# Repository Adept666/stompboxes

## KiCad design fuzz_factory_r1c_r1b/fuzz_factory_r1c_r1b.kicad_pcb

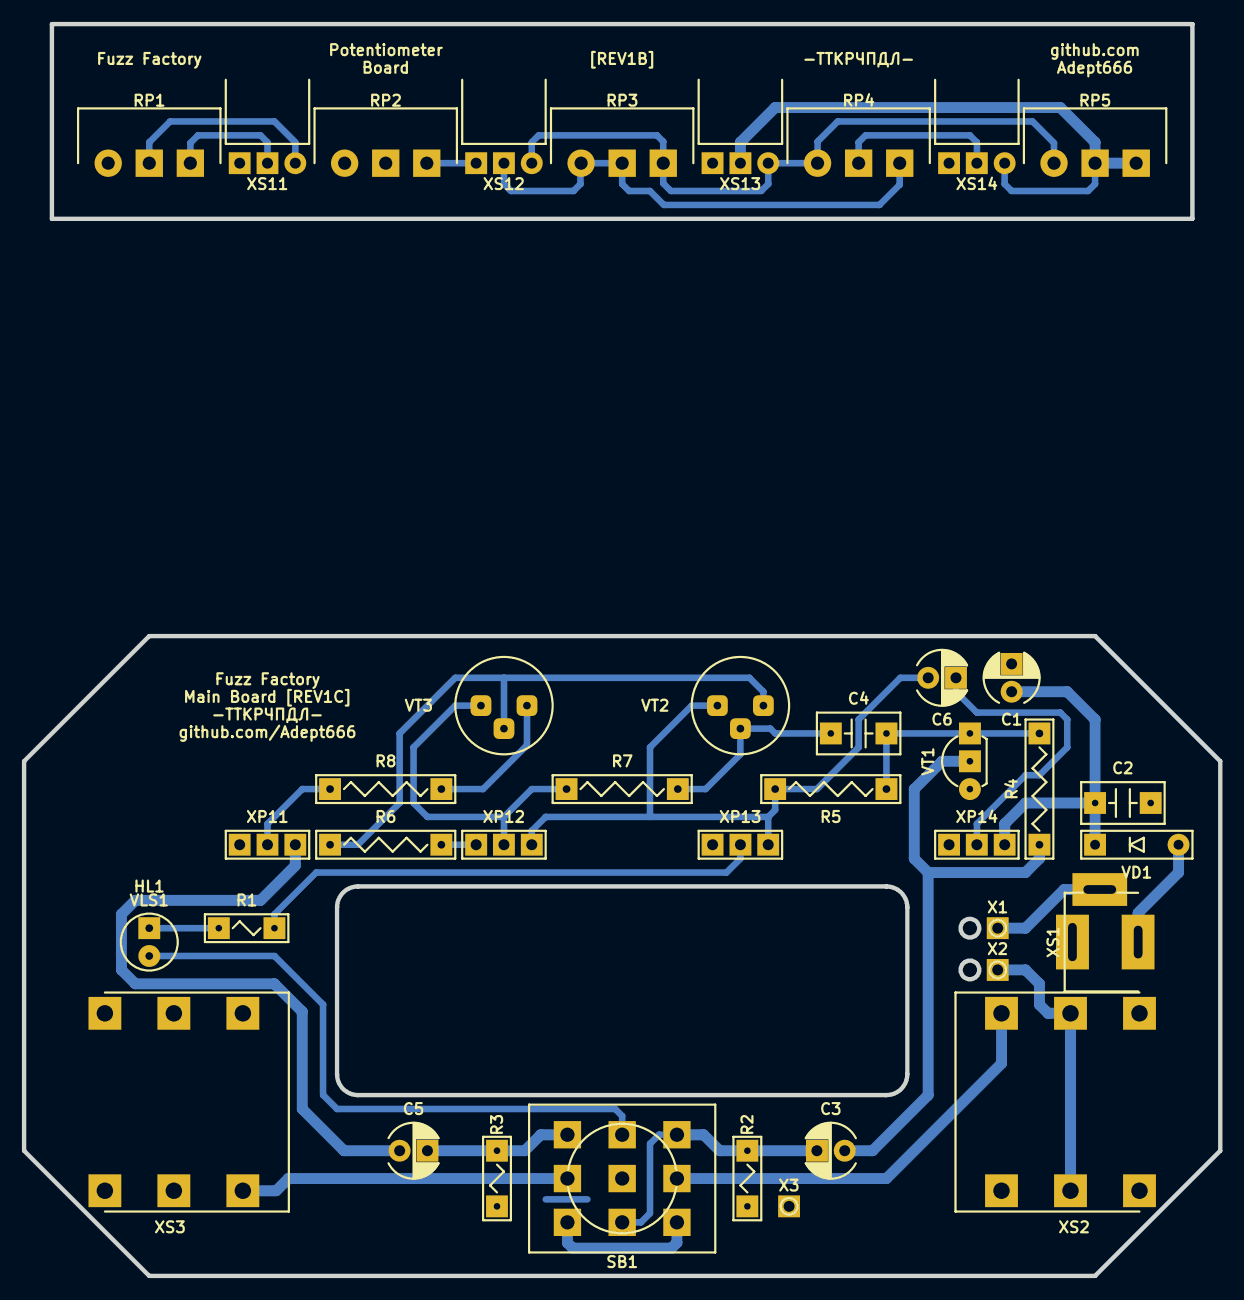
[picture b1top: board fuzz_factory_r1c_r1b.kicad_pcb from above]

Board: 2 copper layers, 109.2 x 114.3 mm, 42 parts (0 on the bottom side), 31 nets.

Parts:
C1: 107; CP-RADIAL-D05.0-P02.0-CLS
C2, C4: 104; C-DISK-D04.2-T03.0-P05.08-d0.5
C3, C5, C6: 106; CP-RADIAL-D05.0-P02.0-CLS
GB1: PP3; B-PP3-HV
HL1: FYL-5013UWC; LED-ROUND-05.0-UNI-SH-SPACER-PNL-5.3
R1: 103; R-MFR-12
R2: 105; R-MFR-12
R3: 224; R-MFR-12
R4: 224; R-MFR-25
R5: 103; R-MFR-25
R6: 471; R-MFR-25
R7: 473; R-MFR-25
R8: 512; R-MFR-25
RP1, RP5: B5K; RP-RK1233N1-L15-KC
RP2, RP3, RP4: B10K; RP-RK1233N1-L15-KC
SB1: PBS-24-302SP; SW-PBS-24-302SP-2.5
VD1: 5817; P-DO-41
VE1: B013; B013_C1
VLS1: BR-17.8; VLS-BR
VT1: 3904; P-TO-92-E-B-C
VT2, VT3: МП40; P-КТЮ-3-6
X1: +; CON-PAD-S-1.0-2.0
X2: -; CON-PAD-S-1.0-2.0
X3: COM; CON-PAD-S-1.0-2.0
XP11, XP12, XP13, XP14: PLS-03; CON-PLS-03
XS1: DC-005; CON-DC-005
XS2, XS3: PJ-644C; CON-PJ-644C
XS11, XS12, XS13, XS14: PBS-03R; CON-PBS-03R

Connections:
/IN-CIR: C3.-, R2.2, SB1.NC2, SB1.NO3
/IN-CON: SB1.COM3, XS2.T
/LED: HL1.C, SB1.NO2
/MB1: R8.1, XP11.2
/MB2: C5.+, XP11.1
/MB3: R6.1, XP12.3
/MB4: R7.2, VT3.E, XP12.2
/MB5: C6.+, R5.2, VT2.E, XP12.1, XP13.1
/MB7: C6.-, XP14.2
/OUT-CIR: C5.-, R3.2, SB1.NO1
/OUT-CON: SB1.COM1, XS3.T
/PB1: RP1.3, XS11.2
/PB2: RP1.2, XS11.1
/PB3: RP2.3, XS12.3
/PB4: RP3.1, RP3.2, RP4.3, XS12.2
/PB5: RP3.3, RP4.1, RP5.1, XS12.1, XS13.1
/PB7: RP4.2, XS14.2
/PBCOM: RP1.1, RP2.1, RP2.2, XS11.3, XS13.3, XS14.3
/PBV: RP5.2, RP5.3, XS13.2, XS14.1
/PP3-NEG: X2.1, XS2.R, XS2.RN
/PP3-POS: X1.1, XS1.SN
COM: C1.-, C2.2, R2.1, R3.1, SB1.COM2, VT1.E, X3.1, XP11.3, XP14.3, XS1.C, XS2.S, XS2.SN, XS2.TN, XS3.R, XS3.RN, XS3.S, XS3.SN
unnamed: C3.+, R4.1, VT1.B
unnamed: C4.1, R4.2, R5.1, VT1.C
unnamed: C4.2, R7.1, VT2.B
unnamed: HL1.A, R1.1
unnamed: R6.2, VT2.C, VT3.B
unnamed: R8.2, VT3.C
unnamed: SB1.NC1, SB1.NC3
unnamed: VD1.A, XS1.S
V: C1.+, C2.1, R1.2, VD1.C, XP13.2, XP14.1

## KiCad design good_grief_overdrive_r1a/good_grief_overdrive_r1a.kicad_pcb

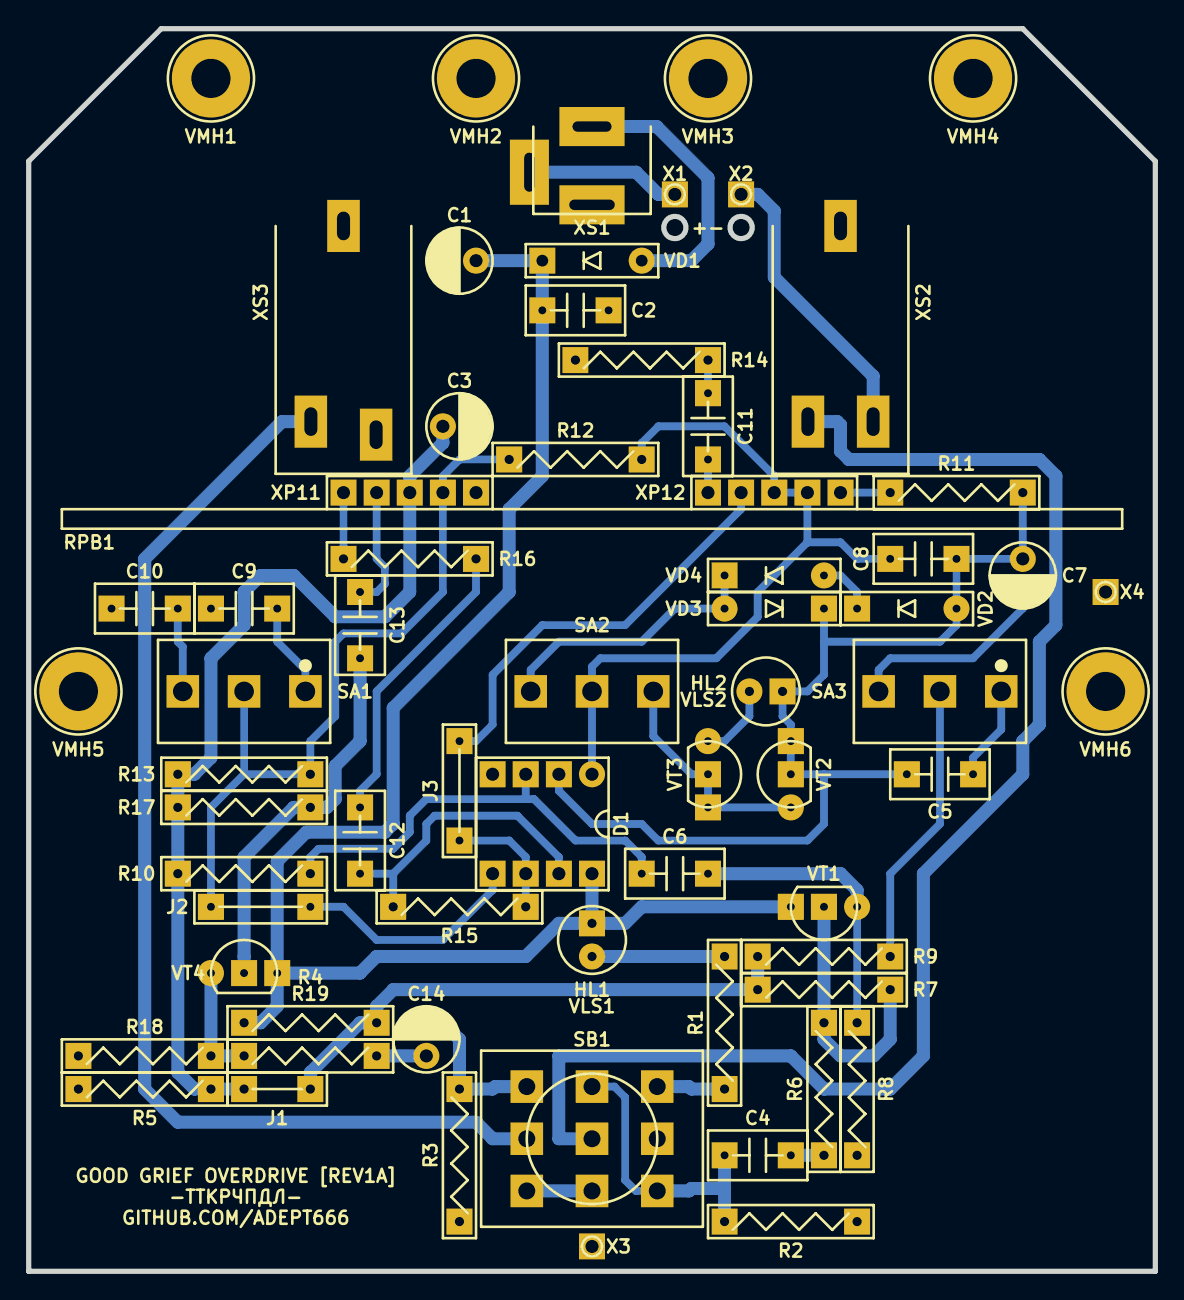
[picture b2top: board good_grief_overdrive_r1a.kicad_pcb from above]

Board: 2 copper layers, 86.4 x 95.3 mm, 69 parts (0 on the bottom side), 40 nets.

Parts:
C1, C3: 476; CP-RADIAL-D05.0-P02.0-CLS
C2, C4, C13: 104; C-DISK-D04.2-T03.0-P05.08-d0.5
C5: 224; C-DISK-D04.2-T03.0-P05.08-d0.5
C6, C12: 105; C-DISK-D04.2-T03.0-P05.08-d0.5
C7, C14: 106; CP-RADIAL-D05.0-P02.0-CLS
C8: 470; C-DISK-D04.2-T03.0-P05.08-d0.5
C9: 154; C-DISK-D04.2-T03.0-P05.08-d0.5
C10: 683; C-DISK-D04.2-T03.0-P05.08-d0.5
C11: 334; C-DISK-D04.2-T03.0-P05.08-d0.5
D1: 833; P-DIP-08
GB1: PP3; B-PP3-HV
HL1: FYL-5013UWC; LED-ROUND-05.0-UNI-SH-SPACER-PNL-5.3
HL2: FYL-5013URC; LED-ROUND-05.0-UNI-SH-SPACER-PNL-5.3
J1: 0.6; J-TH-d0.6-P05.08
J2, J3: 0.5; J-TH-d0.5-P07.62
R1, R3, R4, R5, R8, R13, R18: 103; R-MFR-25
R2: 105; R-MFR-25
R6, R9, R12, R15, R16: 102; R-MFR-25
R7, R17: 564; R-MFR-25
R10, R11: 223; R-MFR-25
R14: 331; R-MFR-25
R19: 101; R-MFR-25
RPB1: B100K-B5K-A500K; RPB-1590BB-18-3x17-1.5-PNL-7.4-2.6
SA1, SA3: MTS-102-A2; SW-MTS-102-A2-2.5-PNL-6.4
SA2: MTS-103-A2; SW-MTS-103-A2-2.5-PNL-6.4
SB1: PBS-24-302SP; SW-PBS-24-302SP-2.5-PNL-13.0
VD1: 5817; P-DO-41
VD2, VD3, VD4: 4148; P-DO-35
VE1: 1590BB; 1590BB_A1
VLS1, VLS2: BR-12.7; VLS-BR
VMH1, VMH2, VMH3, VMH4, VMH5, VMH6: DI5M3x18; VMH-STA-DA5-PNL-3.0
VT1, VT4: MPSA18; P-TO-92-E-B-C
VT2, VT3: 7000; P-TO-92-S-G-D
X1: +; CON-PAD-S-1.0-2.0
X2: -; CON-PAD-S-1.0-2.0
X3, X4: COM; CON-PAD-S-1.0-2.0
XS1: DC-005; CON-DC-005
XS2: ST-008S-04; CON-ST-008X-04
XS3: ST-008S-05; CON-ST-008X-05

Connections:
/IN-CIR: C4.1, R2.2, SB1.NC3, SB1.NO2
/IN-CON: SB1.COM2, XS2.T
/LED: R1.1, SB1.NO3
/OUT-CIR: C14.-, R3.2, SB1.NO1
/OUT-CON: SB1.COM1, XS3.T
/PP3-NEG: X2.1, XS2.R
/PP3-POS: X1.1, XS1.SN
/RP21: D1.5, J2.J, R12.2, R13.1, RPB1.21, SA1.COM
/RP23: D1.6, J3.J, R15.1, RPB1.23
COM: C1.-, C2.2, C3.-, C9.2, C10.2, D1.4, R2.1, R3.1, R5.1, R8.1, R14.1, R18.1, SB1.COM3, VMH1.0, VMH2.0, VMH3.0, VMH4.0, VMH5.0, VMH6.0, X3.1, X4.1, XS1.C, XS2.S, XS3.S
unnamed: C4.2, R6.1
unnamed: C5.1, C7.+, C8.1, D1.2, HL2.A, R11.1, VD2.A, VD3.C, VT2.D, VT2.G
unnamed: C5.2, SA3.NC
unnamed: C6.1, R8.2, VT1.E
unnamed: C6.2, D1.3, R10.2
unnamed: C7.-, SA3.NO
unnamed: C8.2, D1.1, R12.1, RPB1.32, RPB1.33, SA2.COM
unnamed: C9.1, SA1.NC
unnamed: C10.1, SA1.NO
unnamed: C11.1, RPB1.22
unnamed: C11.2, R14.2
unnamed: C12.1, D1.7, R15.2
unnamed: C12.2, R16.1
unnamed: C13.1, RPB1.12
unnamed: C13.2, R17.2, VT4.B
unnamed: C14.+, R19.2
unnamed: HL1.C, R1.2
unnamed: HL2.C, VT3.S
unnamed: R6.2, R7.2, VT1.B
unnamed: R9.2, SA3.COM
unnamed: R11.2, RPB1.31
unnamed: R16.2, RPB1.13
unnamed: R18.2, R19.1, VT4.E
unnamed: SA2.NO_1, VT2.S, VT3.D, VT3.G
unnamed: SA2.NO_2, VD3.A, VD4.C
unnamed: SB1.NC1, SB1.NC2
unnamed: VD1.A, XS1.S
unnamed: VD2.C, VD4.A
V: C1.+, C2.1, D1.8, HL1.A, R4.2, VD1.C, VT1.C, VT4.C
VREF: C3.+, J1.J, R4.1, R5.2, R7.1, R9.1, R10.1, R13.2, R17.1, RPB1.11

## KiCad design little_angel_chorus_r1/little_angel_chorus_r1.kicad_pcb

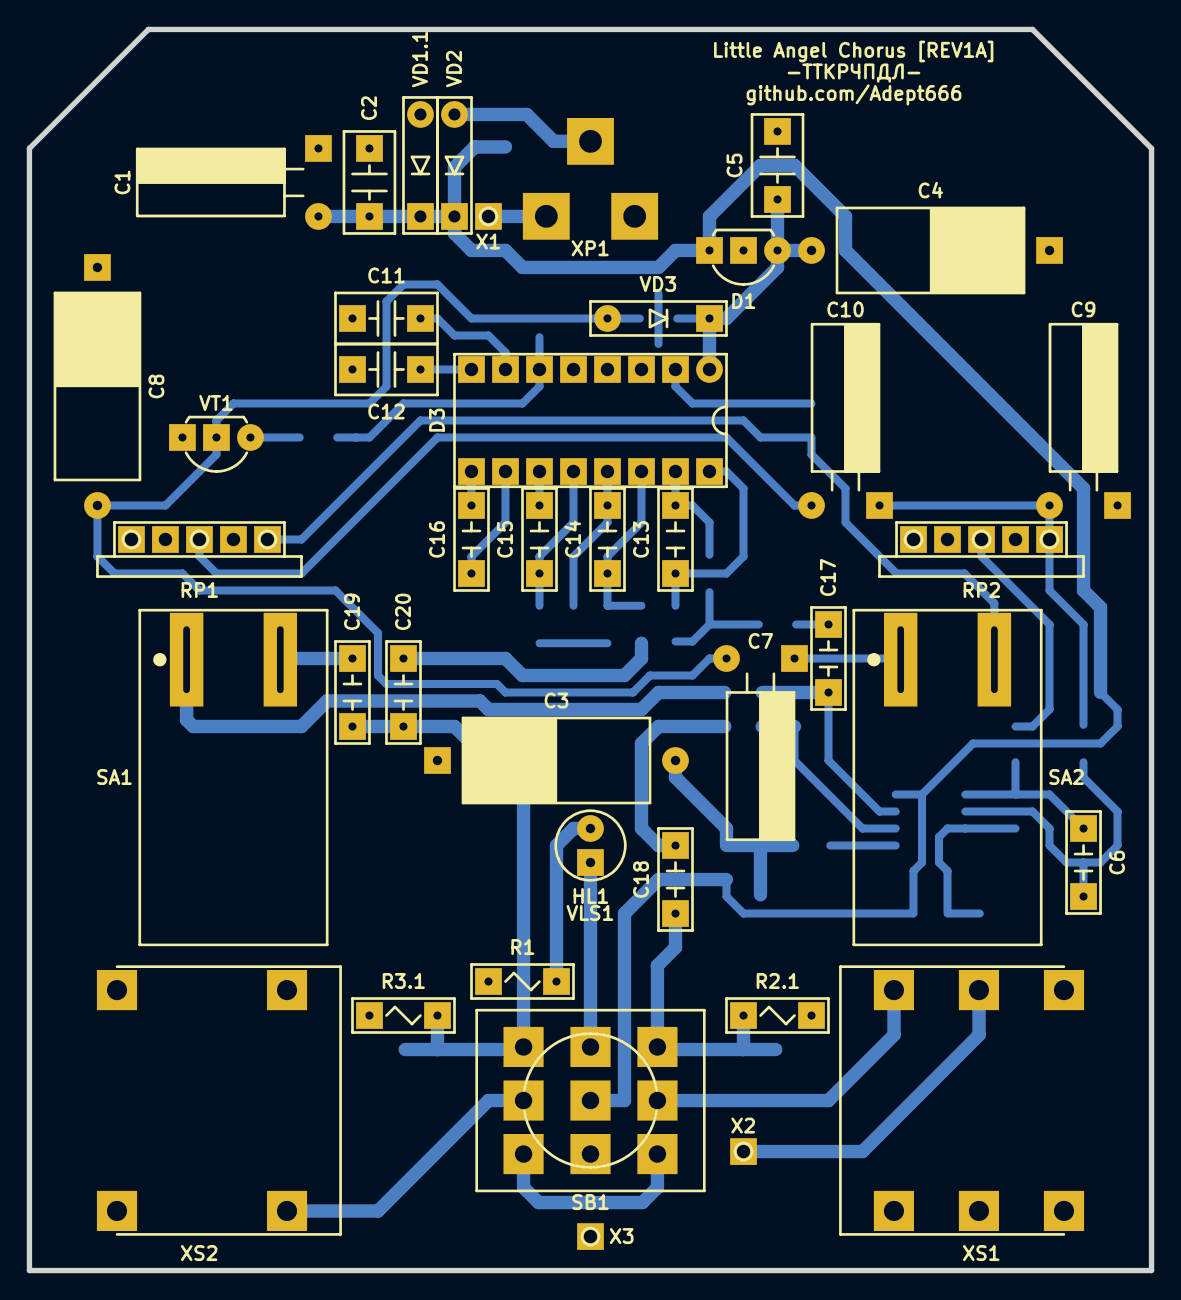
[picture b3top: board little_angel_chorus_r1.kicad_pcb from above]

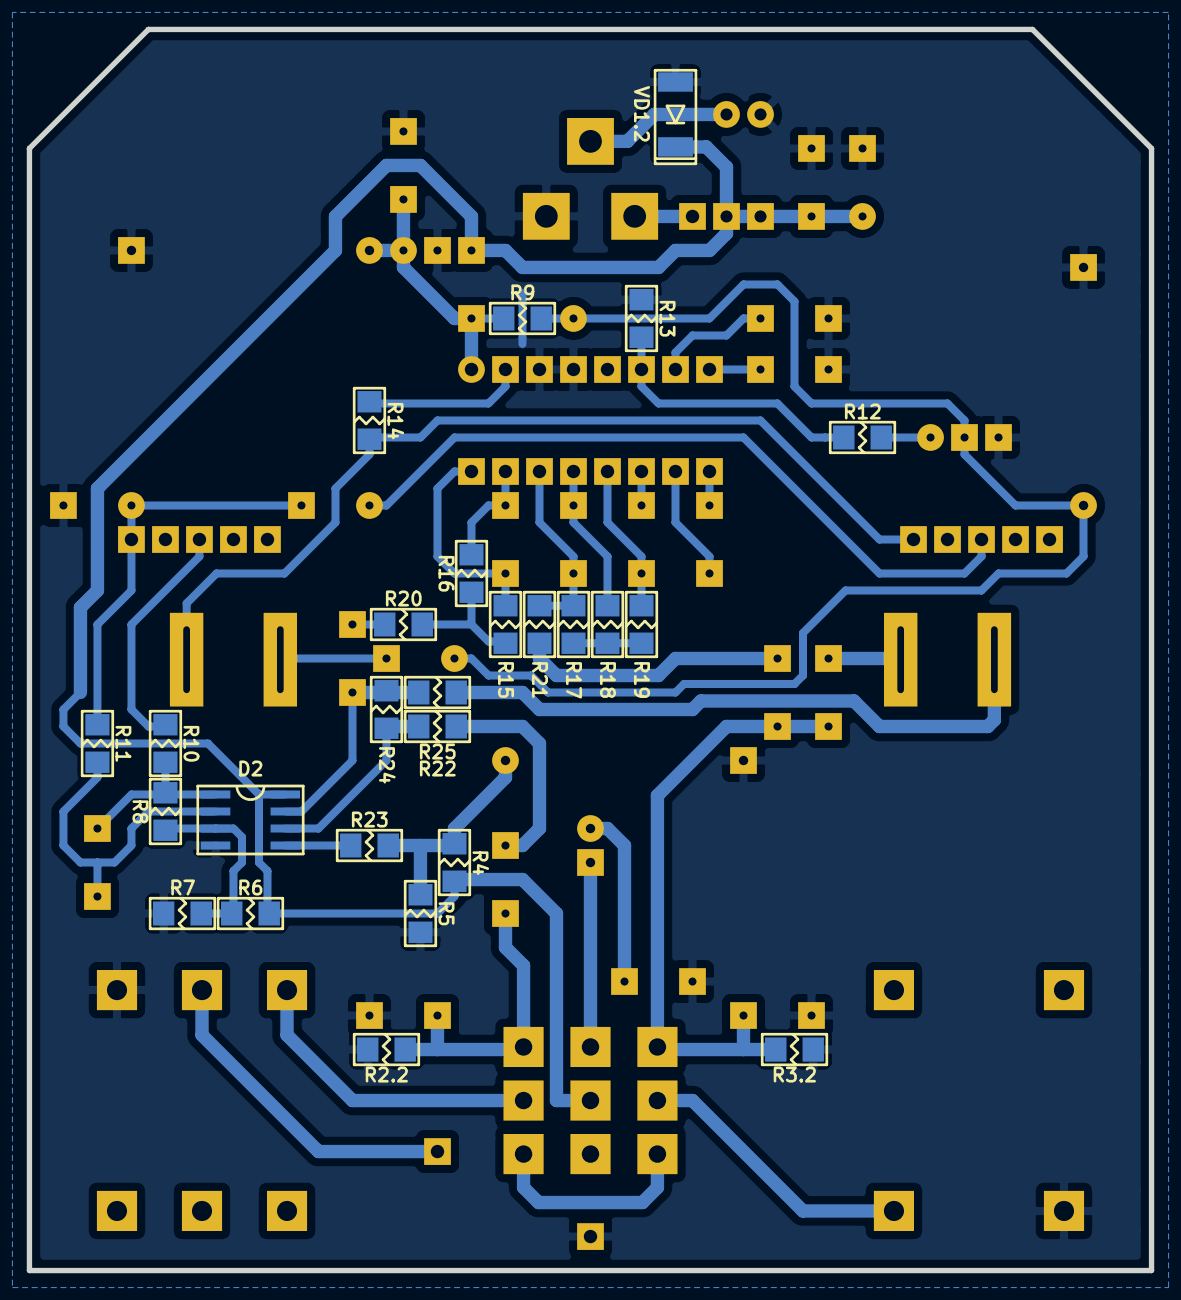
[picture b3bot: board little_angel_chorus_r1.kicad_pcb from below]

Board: 2 copper layers, 83.8 x 92.7 mm, 70 parts (26 on the bottom side), 46 nets.

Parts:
C1: 107; CP-RADIAL-D05.0-P02.0-d0.5-L11-HU
C2, C5, C11, C12: 104; C-DISK-D04.2-T03.0-P05.08-d0.5
C3, C4, C8: 476; CP-AXIAL-D06-L13-d0.6
C6, C15, C16: 103; C-RECT-L07.3-W02.5-P05.08-d0.5
C7: 106; CP-RADIAL-D05.0-P02.0-d0.5-L11-HD
C9, C10: 106; CP-RADIAL-D05.0-P02.0-d0.5-L11-HU
C13: 332; C-RECT-L07.3-W02.5-P05.08-d0.5
C14: 102; C-RECT-L07.3-W02.5-P05.08-d0.5
C17, C18, C19, C20: 104; C-RECT-L07.3-W02.5-P05.08-d0.5
D1: 78L05; P-TO-92-OUT-GND-IN
D2: 5532; P-SO-08
D3: 2399; P-DIP-16
GB1: PP3; B-PP3-HV
HL1: FYL-5013UWC; LED-ROUND-05.0-UNI-SH-SPACER
R1: 103; R-MFR-12
R2.1: 105; R-MFR-12
R2.2, R24: 105; R-SM-1206
R3.1: 104; R-MFR-12
R3.2, R6: 104; R-SM-1206
R4, R5, R15, R16, R17, R18, R19, R20, R21, R25: 103; R-SM-1206
R7: 473; R-SM-1206
R8, R11: 224; R-SM-1206
R9: 683; R-SM-1206
R10: 472; R-SM-1206
R12: 101; R-SM-1206
R13: 222; R-SM-1206
R14: 333; R-SM-1206
R22: 474; R-SM-1206
R23: 334; R-SM-1206
RP1, RP2: B50K; RP-RK1233N1-KC-PCB
SA1, SA2: KN3-1; SW-KN3-1-PCB
SB1: PBS-24-302SP; SW-PBS-24-302SP
VD1.1: 400x; P-DO-41
VD1.2: 4001; P-SOD-87
VD2: 5817; P-DO-41
VD3: 4148; P-DO-35
VE1: G0473; G0473_little_angel_chorus_r1a
VLS1: BR-17.8; VLS-BR
VT1: 3904; P-TO-92-C-B-E
X1: +; CON-PAD-S-1.0-2.0
X2: -; CON-PAD-S-1.0-2.0
X3: COM; CON-PAD-S-1.0-2.0
XP1: 722RA; CON-(L)7X2RA(H)
XS1: NYS215; CON-NYS-215
XS2: NYS2152; CON-NYS-2152

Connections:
/IN-CON: SB1.COM3, XS1.T
/IN-SCH: C18.1, R2.1.2, R2.2.2, SB1.NO3
/LED: HL1.A, SB1.NO2
/OUT-CON: SB1.COM1, XS2.T
/OUT-SCH: C19.2, C20.2, R3.1.2, R3.2.2, SB1.NO1
/PP3-NEG: X2.1, XS1.R
/PP3-POS: X1.1, XP1.SN
COM: C1.-, C2.2, C3.-, C4.-, C5.2, C8.-, C9.-, C11.1, C12.1, D1.GND, D2.4, D3.3, D3.4, R1.1, R2.1.1, R2.2.1, R3.1.1, R3.2.1, R5.1, R7.1, R13.1, VD1.1.A, VD1.2.A, VT1.E, X3.1, XP1.C, XS1.S, XS2.S
unnamed: C6.1, D2.1, R8.2, R10.1
unnamed: C6.2, D2.2, R11.1
unnamed: C7.+, C8.+, R9.1, VD3.A, VT1.B
unnamed: C7.-, SA2.COM
unnamed: C10.+, RP1.2
unnamed: C9.+, C10.-, R11.2, RP2.3
unnamed: C11.2, D3.7
unnamed: C12.2, D3.8
unnamed: C13.1, D3.16, R15.1
unnamed: C13.2, D3.15, R16.1
unnamed: C14.1, D3.14, R17.1, R21.1
unnamed: C14.2, D3.13, R18.1
unnamed: C15.1, D3.12, R19.1
unnamed: C15.2, D3.11
unnamed: C16.1, D3.10
unnamed: C16.2, D3.9
unnamed: C17.1, R20.2
unnamed: C17.2, D2.7, R24.2, R25.1
unnamed: C18.2, R22.1
unnamed: C19.1, SA1.NO
unnamed: C20.1, R21.2
unnamed: D2.5, R23.2
unnamed: D2.6, R22.2, R24.1
unnamed: D3.2, R14.2
unnamed: D3.6, R12.2, R13.2
unnamed: HL1.C, R1.2
unnamed: R10.2, RP2.2
unnamed: R12.1, VT1.C
unnamed: R14.1, RP1.3, SA2.NO
unnamed: R15.2, R16.2, R20.1
unnamed: R17.2, R18.2, R19.2
unnamed: R25.2, SA1.COM
unnamed: SB1.NC1, SB1.NC3
unnamed: VD2.A, XP1.S
V: C1.+, C2.1, D1.IN, D2.8, R4.2, R6.2, SB1.COM2, VD1.1.C, VD1.2.C, VD2.C
VA: C4.+, C5.1, D1.OUT, D3.1, R9.2, VD3.C
VB: C3.+, R4.1, R5.2, R23.1
VC: D2.3, R6.1, R7.2, R8.1

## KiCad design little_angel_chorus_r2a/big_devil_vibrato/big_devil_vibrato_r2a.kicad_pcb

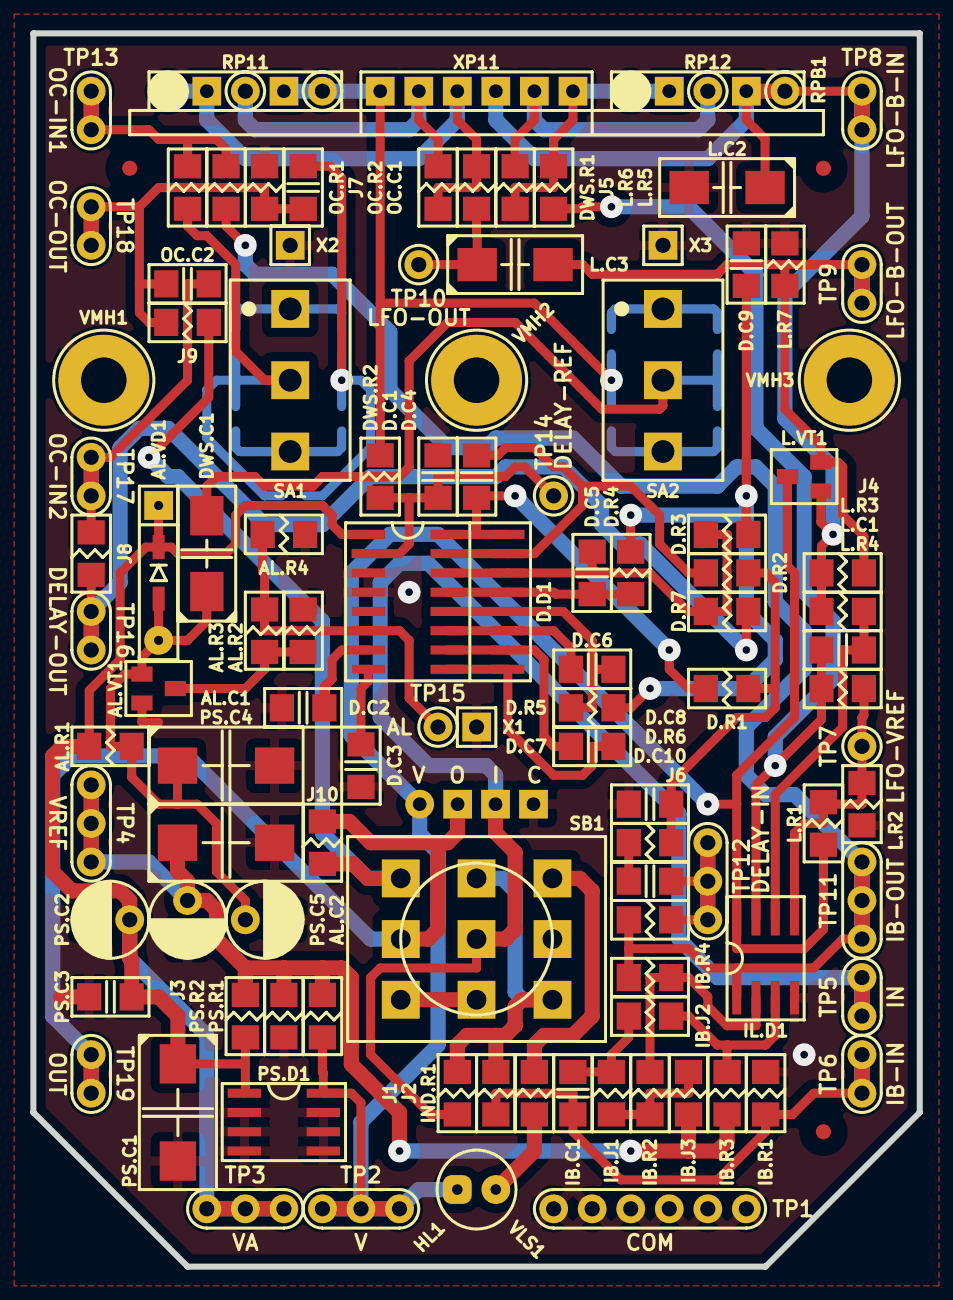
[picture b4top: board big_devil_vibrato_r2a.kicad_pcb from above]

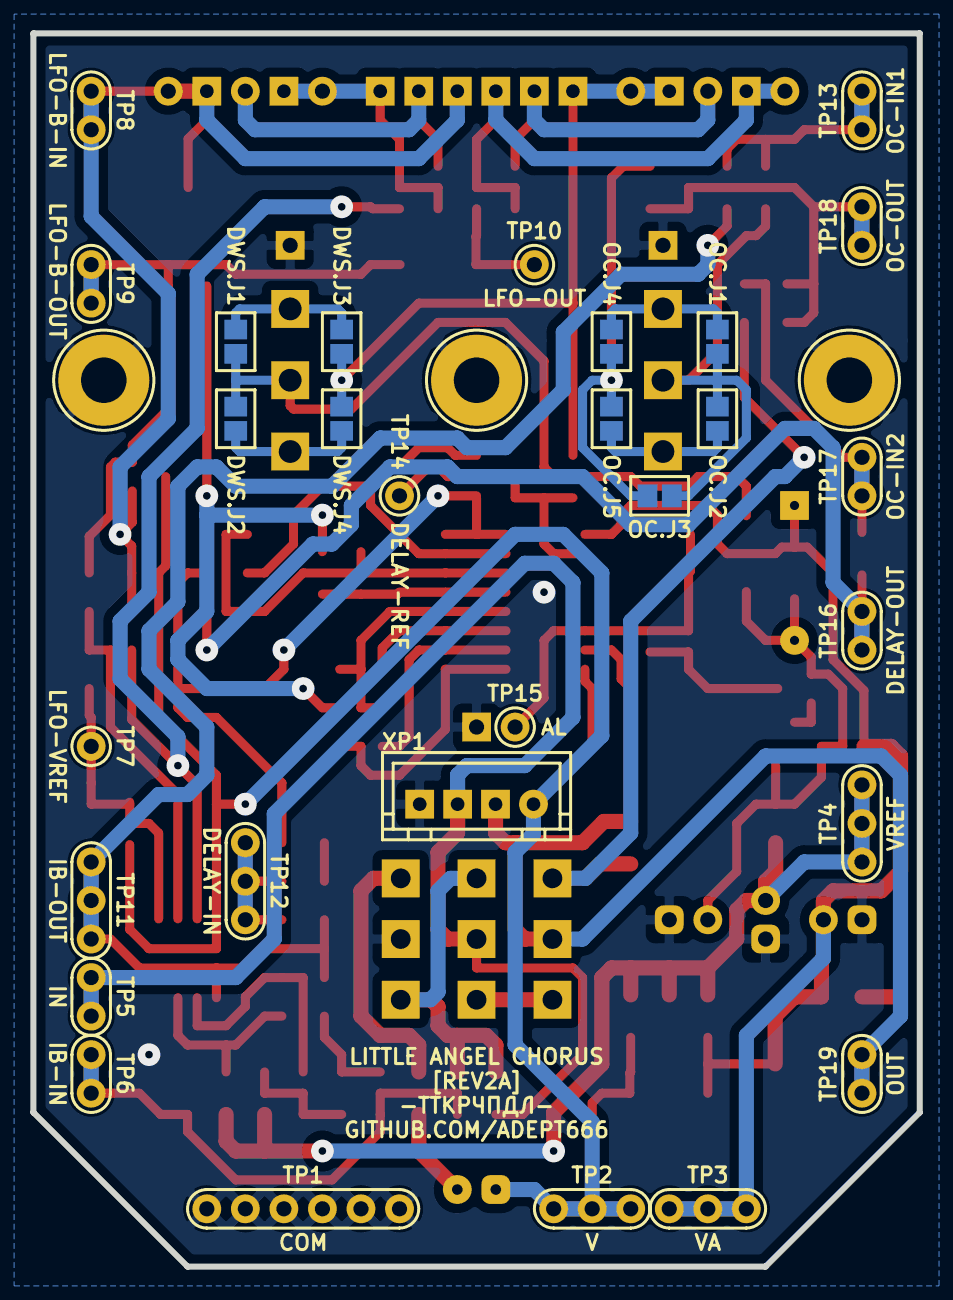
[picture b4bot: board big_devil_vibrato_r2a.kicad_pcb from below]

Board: 2 copper layers, 58.4 x 81.3 mm, 118 parts (10 on the bottom side), 57 nets.

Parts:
AL.C1: 476; CP-CTSMD-D
AL.C2: 476; CP-RADIAL-D05.0-P02.0-CLS
AL.R1: 683; R-SM-1206
AL.R2: X; R-SM-1206
AL.R3: 101; R-SM-1206
AL.R4: 222; R-SM-1206
AL.VD1: 4148; P-SOD-123-OR-DO-35-V2
AL.VT1: 3904; P-SOT-23-B-E-C
D.C1: 105; C-SM-1206
D.C2, D.C3, D.C10: 104; C-SM-1206
D.C4, D.C8, D.C9: 332; C-SM-1206
D.C5: 102; C-SM-1206
D.C6, D.C7: 103; C-SM-1206
D.D1: 8970; P-SO-16-OR-SO-16W
D.R1, D.R2, D.R3, D.R4, D.R5, D.R6, D.R7: 103; R-SM-1206
DWS.C1: X; CP-CTSMD-C
DWS.J1: DWS.J1; J-SB-0805-2
DWS.J2: DWS.J2; J-SB-0805-2
DWS.J3: DWS.J3; J-SB-0805-2
DWS.J4: DWS.J4; J-SB-0805-2
DWS.R1: 0; R-SM-1206
DWS.R2: 333; R-SM-1206
HL1: FYL-5013UWC; LED-ROUND-05.0-UNI-SH-SPACER-PNL-5.3
IB.C1: 104; C-SM-1206
IB.J1: X; R-SM-1206
IB.J2, IB.J3: 0; R-SM-1206
IB.R1: 105; R-SM-1206
IB.R2, IB.R4: 223; R-SM-1206
IB.R3: 474; R-SM-1206
IL.D1: 5532; P-SO-08
IND.R1: 103; R-SM-1206
J1, J3, J4, J7, J10: X; R-SM-1206
J2, J5, J6, J8, J9: 0; R-SM-1206
L.C1: 103; C-SM-1206
L.C2, L.C3: 106; CP-CTSMD-C
L.R1: 104; R-SM-1206
L.R2: 473; R-SM-1206
L.R3, L.R4: 224; R-SM-1206
L.R5: 472; R-SM-1206
L.R6: 0; R-SM-1206
L.R7: 103; R-SM-1206
L.VT1: 3904; P-SOT-23-B-E-C
OC.C1: X; C-SM-1206
OC.C2: 104; C-SM-1206
OC.J1: OC.J1; J-SB-0805-2
OC.J2: OC.J2; J-SB-0805-2
OC.J3: OC.J3; J-SB-0805-2
OC.J4: OC.J4; J-SB-0805-2
OC.J5: OC.J5; J-SB-0805-2
OC.R1: X; R-SM-1206
OC.R2: 104; R-SM-1206
PS.C1, PS.C4: 476; CP-CTSMD-D
PS.C2, PS.C5: 476; CP-RADIAL-D05.0-P02.0-CLS
PS.C3: 104; C-SM-1206
PS.D1: 78L05; P-SO-08-OUT-GND-GND-NC-NC-GND-GND-IN
PS.R1, PS.R2: 103; R-SM-1206
RPB1: B50K-B50K; RPB-1590N1-18-2x17-OR-2x1x17-1.6-PNL-7.4-2.8
SA1, SA2: X; SW-MTS-102-A2-2.5-PNL-6.0
SB1: PBS-24-302SP; SW-PBS-24-302SP-2.5-PNL-13.0
TP1: COM; TP-6-1.0-1.9
TP2: V; TP-3-1.0-1.9
TP3: VA; TP-3-1.0-1.9
TP4: VREF; TP-3-1.0-1.9
TP5: IN; TP-2-1.0-1.9
TP6: IB-IN; TP-2-1.0-1.9
TP7: LFO-VREF; TP-1-1.0-1.9
TP8: LFO-B-IN; TP-2-1.0-1.9
TP9: LFO-B-OUT; TP-2-1.0-1.9
TP10: LFO-OUT; TP-1-1.0-1.9
TP11: IB-OUT; TP-3-1.0-1.9
TP12: DELAY-IN; TP-3-1.0-1.9
TP13: OC-IN1; TP-2-1.0-1.9
TP14: DELAY-REF; TP-1-1.0-1.9
TP15: AL; TP-1-1.0-1.9
TP16: DELAY-OUT; TP-2-1.0-1.9
TP17: OC-IN2; TP-2-1.0-1.9
TP18: OC-OUT; TP-2-1.0-1.9
TP19: OUT; TP-2-1.0-1.9
VE1: 1590N1; 1590N1_A1
VFM1, VFM2, VFM3: 1.0; VFM-1.0-3.0-SL
VLS1: BR-12.7; VLS-BR
VMH1, VMH3: DI5M3x18; VMH-STA-DA5-PNL-3.0
VMH2: X; VMH-STA-DA5-PNL-3.0
X1: COM; CON-PAD-S-1.0-1.9
X2, X3: X; CON-PAD-S-1.0-1.9
XB1: 1590N1 Connector Board; XB-1590N1
XP1: B4B-XH-A; CON-XH-B4B-A

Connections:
/AL: AL.R3.2, AL.R4.2, D.D1.6, TP15.1
/CIR-IN: J1.2, J2.1, SB1.NC3, SB1.NO2
/CIR-OUT: J9.2, J10.1, SB1.NO1
/DELAY-IN: D.C10.2, J6.2, TP12.1
/DELAY-OUT: D.R7.2, J8.1, TP16.1
/DELAY-REF: D.C1.1, D.D1.2, DWS.R2.2, TP14.1
/DEPTH-IN: DWS.R1.1, J5.2, RPB1.11, RPB1.NC1
/IB-IN: IB.C1.1, IB.R1.2, J2.2, TP6.1
/IB-OUT: IB.R4.2, IL.D1.1, J6.1, J7.1, TP11.1
/IN: J1.1, SB1.COM2, TP5.1, XP1.3
/LED: IND.R1.1, SB1.NO3
/LFO-B-IN: J4.1, L.C2.+, L.R3.2, L.VT1.B, RPB1.23, RPB1.NC4, TP8.1
/LFO-B-OUT: J4.2, L.C3.-, L.R7.2, L.VT1.E, TP9.1
/LFO-OUT: J5.1, L.C3.+, TP10.1
/LFO-VREF: IL.D1.5, L.R1.1, L.R2.2, L.R4.1, TP7.1
/OC-IN1: J7.2, OC.R1.1, TP13.1
/OC-IN2: J8.2, OC.C2.1, TP17.1
/OC-OUT: J9.1, OC.C1.2, OC.C2.2, OC.R2.2, TP18.1
/OUT: J10.2, SB1.COM1, TP19.1, XP1.2
/WS: AL.C1.+, AL.C2.+, AL.R1.1, AL.VD1.A, AL.VT1.B, DWS.C1.+
COM: AL.C1.-, AL.C2.-, AL.R2.1, AL.R4.1, AL.VT1.E, D.C1.2, D.C2.1, D.C3.1, D.C8.1, D.C9.2, D.D1.3, D.D1.4, IB.R1.1, IL.D1.4, L.C2.-, L.R2.1, L.R7.1, OC.R2.1, PS.C1.-, PS.C2.-, PS.C3.2, PS.C4.-, PS.C5.-, PS.D1.GND, PS.D1.NC, PS.R2.1, SB1.COM3, TP1.1, VMH1.0, VMH2.0, VMH3.0, X1.1, X2.1, X3.1, XP1.4
unnamed: AL.R2.2, AL.R3.1, AL.VT1.C
unnamed: D.C2.2, D.D1.7
unnamed: D.C3.2, D.D1.8
unnamed: D.C4.1, D.D1.16, D.R1.1
unnamed: D.C4.2, D.D1.15, D.R2.1
unnamed: D.C5.1, D.D1.14, D.R3.1, D.R7.1
unnamed: D.C5.2, D.D1.13, D.R4.1
unnamed: D.C6.1, D.D1.12, D.R5.1
unnamed: D.C6.2, D.D1.11
unnamed: D.C7.1, D.D1.10
unnamed: D.C7.2, D.D1.9
unnamed: D.C8.2, D.R1.2, D.R2.2, D.R6.1
unnamed: D.C9.1, D.R3.2, D.R4.2, D.R5.2
unnamed: D.C10.1, D.R6.2
unnamed: DWS.C1.-, DWS.J1.1, DWS.J2.1, SA2.COM
unnamed: DWS.J1.2, DWS.J3.1, SA2.NC
unnamed: DWS.J2.2, DWS.J4.1, SA2.NO
unnamed: DWS.J3.2, DWS.J4.2, DWS.R2.1, RPB1.13, RPB1.NC2
unnamed: DWS.R1.2, RPB1.12
unnamed: HL1.C, IND.R1.2
unnamed: IB.C1.2, IB.J1.1, IB.J2.1
unnamed: IB.J1.2, IB.J3.2, IB.R2.1
unnamed: IB.J2.2, IB.R3.2, IL.D1.3
unnamed: IB.R2.2, IB.R4.1, IL.D1.2
unnamed: IL.D1.6, L.C1.1, L.R3.1
unnamed: IL.D1.7, L.C1.2, L.R4.2, L.R5.1
unnamed: L.R5.2, L.R6.1, RPB1.21, RPB1.NC3
unnamed: L.R6.2, RPB1.22
unnamed: OC.C1.1, OC.J3.2, OC.J4.2, OC.J5.2
unnamed: OC.J1.1, OC.J2.1, OC.J3.1, OC.R1.2, SA1.COM
unnamed: OC.J1.2, OC.J4.1, SA1.NC
unnamed: OC.J2.2, OC.J5.1, SA1.NO
unnamed: SB1.NC1, SB1.NC2
V: HL1.A, IL.D1.8, L.R1.2, L.VT1.C, PS.D1.IN, PS.R1.2, TP2.1, XP1.1
VA: AL.R1.2, AL.VD1.C, D.D1.1, J3.1, PS.C1.+, PS.C2.+, PS.C3.1, PS.D1.OUT, TP3.1
VREF: IB.J3.1, IB.R3.1, J3.2, PS.C4.+, PS.C5.+, PS.R1.1, PS.R2.2, TP4.1

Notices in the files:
fuzz_factory_r1c_r1b/fuzz_factory_r1c_r1b.kicad_pcb:
This project is licensed under GNU General Public License v3.0 or later
